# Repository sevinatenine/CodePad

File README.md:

# CodePad

CodePad is a custom hack pad (macro pad) with 6 keys, a rotary encoder and a screen!
I designed this project for the Stardance Hackpad mission.

## Features

- 128x32 OLED Display
- EC11 Rotary encoder (for volume/anything)
- 6 Cherry MX-style keys

## CAD

CodePad is printed in two pieces, the lid and the case.
There are 4 screws that go through the lid, sqeeze down the pcb and go into threaded inserts in the bottom case.
You will need 4 M3 bolts and the threaded inserts for them.
This was made in Fusion360.

## PCB

The PCB was made in KiCad. I added a ground plane.

## Firmware

The firmware is built for CircuitPython and the code is in the [`firmware`](./firmware) folder.
You will need to install CircuitPython on the device and the necessary librarie, then upload the [`code.py`](./firmware/code.py).

## BOM

- 6x [Cherry MX Switches](https://www.amazon.com/Deftomo-Keyboard-Switches-Mechanical-Replacement/dp/B0FSWLNL21) (~$0.96)
- 6x [DSA Keycaps](https://www.amazon.com/Mechkeeb-Profile-Switches-Keyboard-Replacement/dp/B0BWDTBF1L) (~$2.25)
- 1x [0.91" 128x32 OLED Display](https://www.amazon.com/dp/B0F3CXTWZT) (~$7.99)
- 1x [EC11 Rotary Encoder](https://www.amazon.com/DIYhz-Rotary-Encoder-Digital-Potentiometer/dp/B07D3DF8TK) (~$1.00)
- 1x [XIAO RP2040](https://www.seeedstudio.com/XIAO-RP2040-v1-0-p-5026.html) (~$3.99)
- 4x [M3 bolts](https://www.amazon.com/Machine-Screws-Countersunk-Phillips-Assortment/dp/B0CCPH974T) (~$0.07)
- 4x [M3 heat-set threaded inserts](https://www.amazon.com/dp/B0FDKYTMZ8) (~$0.26)
- 1x Case (2 3D printed parts) (Print the [case](production/Case.stl) and [lid](production/Lid.stl)).
- 1x PCB (2 layer) (The gerbers are [here](production/gerbers.zip)). Can be manufactured by a company such as [JLCPCB](https://jlcpcb.com) (~$2.00).

**Estimated total: ~$18.52** (prorated from multi-packs, so you'll actually pay more up front for the full packs).

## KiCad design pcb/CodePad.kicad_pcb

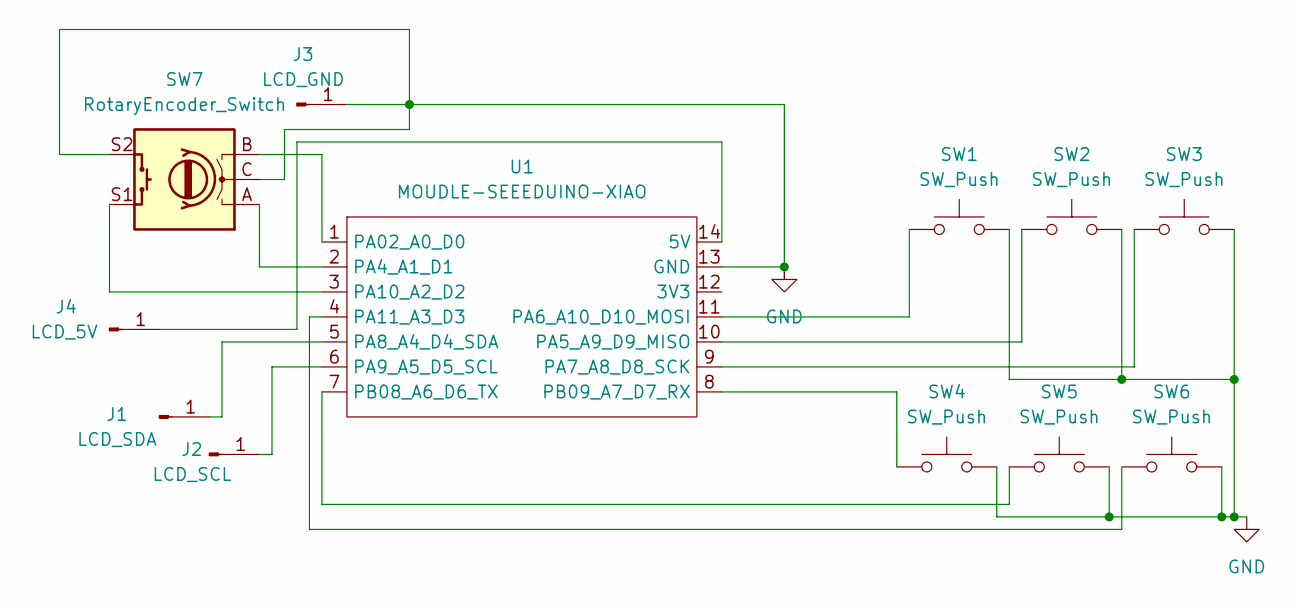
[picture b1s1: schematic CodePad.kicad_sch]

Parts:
J1: LCD_SDA; TestPoint_THTPad_2.0x2.0mm_Drill1.0mm
J2: LCD_SCL; TestPoint_THTPad_2.0x2.0mm_Drill1.0mm
J3: LCD_GND; TestPoint_THTPad_2.0x2.0mm_Drill1.0mm
J4: LCD_5V; TestPoint_THTPad_2.0x2.0mm_Drill1.0mm
SW1, SW2, SW3, SW4, SW5, SW6: SW_Push; SW_Cherry_MX_1.00u_PCB
SW7: RotaryEncoder_Switch; RotaryEncoder_Alps_EC11E-Switch_Vertical_H20mm
U1: MOUDLE-SEEEDUINO-XIAO; XIAO-Generic-Hybrid-14P-2.54-21X17.8MM

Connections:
GND: J3.1, SW1.2, SW2.2, SW3.2, SW4.2, SW5.2, SW6.2, SW7.C, SW7.S2, U1.13 (GND)
unnamed: J1.1, U1.5 (PA8_A4_D4_SDA)
unnamed: J2.1, U1.6 (PA9_A5_D5_SCL)
unnamed: J4.1, U1.14 (5V)
unnamed: SW7.B, U1.1 (PA02_A0_D0)
unnamed: SW7.A, U1.2 (PA4_A1_D1)
unnamed: SW2.1, U1.10 (PA5_A9_D9_MISO)
unnamed: SW1.1, U1.11 (PA6_A10_D10_MOSI)
unnamed: SW3.1, U1.9 (PA7_A8_D8_SCK)
unnamed: SW7.S1, U1.3 (PA10_A2_D2)
unnamed: SW6.1, U1.4 (PA11_A3_D3)
unnamed: SW5.1, U1.7 (PB08_A6_D6_TX)
unnamed: SW4.1, U1.8 (PB09_A7_D7_RX)

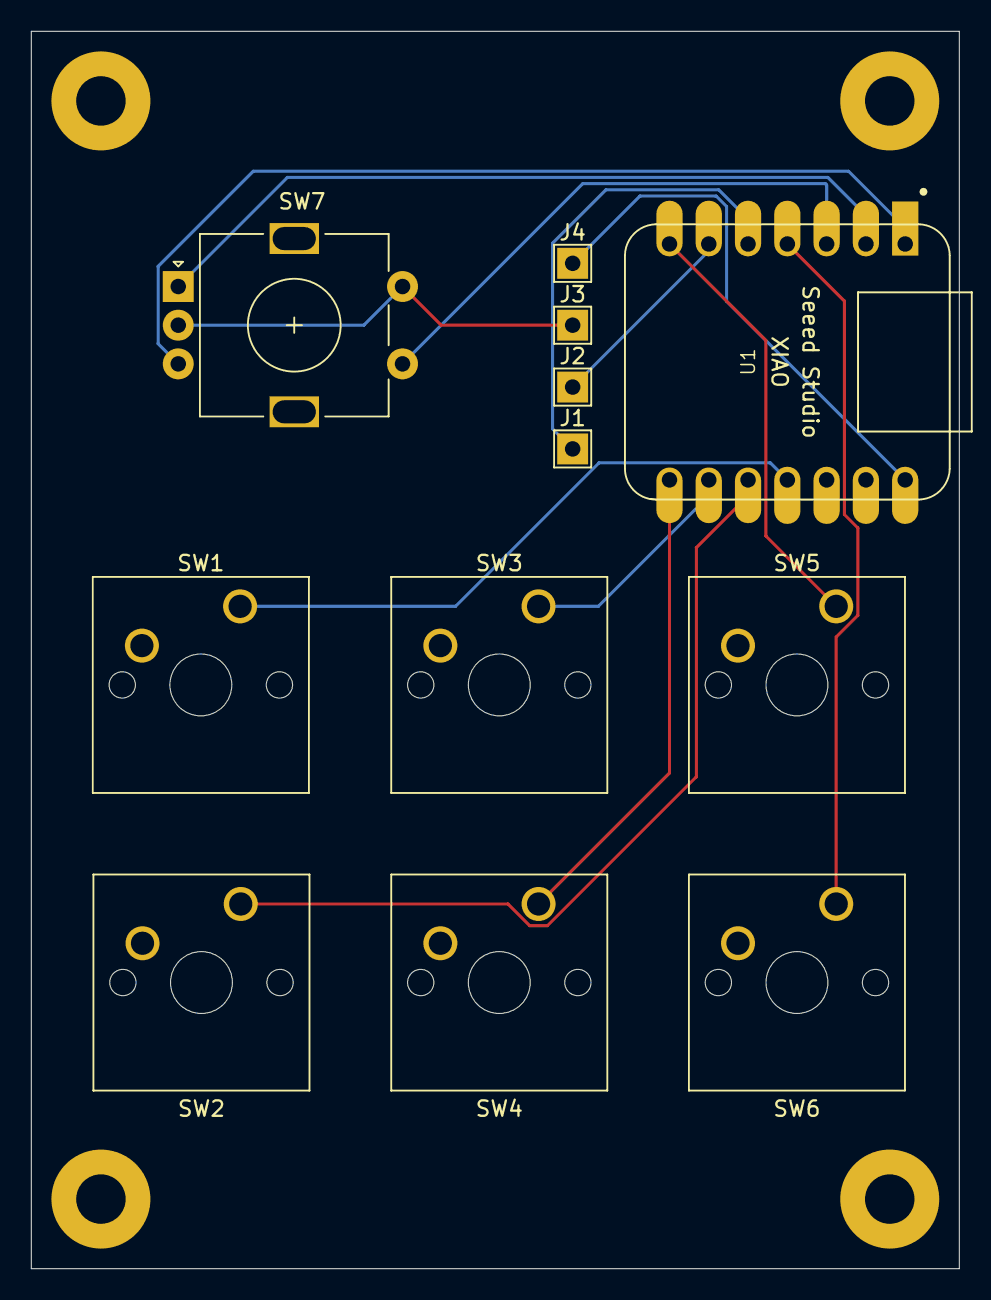
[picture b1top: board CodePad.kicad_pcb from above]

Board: 2 copper layers, 60.0 x 80.0 mm, 12 parts (0 on the bottom side), 13 nets.
